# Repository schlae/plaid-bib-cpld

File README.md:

# The Plaid Bib CPLD edition - an Ad Lib MCA Clone

The Plaid Bib is a 100% compatible clone of the Ad Lib MCA sound card. This is
an Ad Lib card designed for Micro Channel Architecture machines, such as the
IBM PS/2 family and other compatibles from NCR, Tandy, Dell, and others.

Here are the design files. The BOM includes Mouser Electronics part numbers for
everything except for the YM3812 and the Y3014B, both of which are available
from brokers in China such as UTSource.

[Schematic](https://github.com/schlae/plaid-bib-cpld/blob/master/PlaidBibCPLD.pdf)

[Bill of Materials](https://github.com/schlae/plaid-bib-cpld/blob/master/PlaidBibCPLD.csv)

[Fab Files](https://github.com/schlae/plaid-bib-cpld/blob/master/fab/PlaidBibCPLD-fab.zip)

The logic family used for U1 is critical. Do not substitute LS, HC, HCT, or
similarly slow logic families. Use ALS, ACT, AHCT, or even F.

It's a good idea to use sockets for all the DIP chips just in case you need
to swap parts out.

## CPLD Notes
The Plaid Bib uses a CPLD (Complex Programmable Logic Device) to interface
between the MCA bus and the YM3812 synthesizer chip. Compared with the original
design that uses the 82C611 interface chip, this version is much simpler and
incorporates much of the external logic into a single device.

The CPLD must be programmed with the bitstream before you can use the card.
[You can find the bitstream here.](https://github.com/schlae/plaid-bib-cpld/blob/master/cpld/mcadlib.jed)

I've had good luck using the Linux command line program 'xc3sprog' with a
FTDI FT2232H Mini Module [datasheet here](https://www.ftdichip.com/Support/Documents/DataSheets/Modules/DS_FT2232H_Mini_Module.pdf).

Wiring for the FT2232H mini module:

| Point 1    | Point 2          | Description           |
| ---------- | ---------------- | --------------------- |
| CN2 pin 1  | CN2 pin 11       | V3V3 to VIO strap     |
| CN3 pin 1  | CN3 pin 3        | VBUS to VCC strap     |
| CN2 pin 3  | CN3 pin 12       | V3V3 to VIO strap (2) |
| CN2 pin 5  | JTAG cable pin 6 | V3V3 to Plaid Bib (optional) |
| CN2 pin 2  | JTAG cable pin 5 | GND                   |
| CN2 pin 7  | JTAG cable pin 4 | AD0, aka TCK          |
| CN2 pin 9  | JTAG cable pin 3 | AD2, aka TDO          |
| CN2 pin 10 | JTAG cable pin 2 | AD1, aka TDI          |
| CN2 pin 12 | JTAG cable pin 1 | AD3, aka TMS          |

You need to provide external power to the Plaid Bib through the 3.3V wire on the
programming header. The optional wire does this, or you can use a bench supply.

I obtained xc3sprog [here](https://github.com/matrix-io/xc3sprog). You can
compile and run this program on a Raspberry Pi using the Pi GPIO lines instead
of the FTDI mini module. In my case, I chose to patch it (TBD) to remove
references to the Pi GPIO library and ran it on a regular Linux PC.

Using the FTDI mini module, programming is quite simple. Connect the cable to
the assembled Plaid Bib board, then run the following command.

`xc3sprog -c ftdi -v mcadlib.jed`

If you run into issues with the cable not being detected, check your udev rules.
In theory you could run xc3sprog as root, but that's bad practice. ;)

### Building the CPLD Project
If you're feeling particularly masochistic, you can try building the CPLD
project using the Xilinx ISE Webpack tools. Because the ISE Webpack only
supports Ubuntu 14.7, it's simplest to run the program from a Docker container.
I use [docker-xilinx](https://github.com/jimmo/docker-xilinx).

### How the CPLD Works
This isn't meant to be an exhaustive tutorial on how Micro Channel bus works,
but here are a few basic functions the CPLD provides:
- Card setup and POS (programmable option select)
- Address decoding logic
- MCA bus logic interface to the YM3812
- A clock divider to provide 3.57MHz to the YM3812

Each card implements several 8-bit registers (POS registers). Two of these
registers are fixed and implement the 16-bit card ID value, which is how the
BIOS and the reference disk software identify the card. The remaining POS
registers can be used for any configuration-related function and are designed
to replace configuration jumpers. The meanings of each register bit are up
to the card designer, with the exception of a reserved bit that is used by
the BIOS to enable or disable a card; this way, the BIOS can resolve conflicts
automatically. Typically POS register bits control IO and memory address
assignments, IRQ lines, and so forth.

The CPLD implements the two required ID registers as well as two additional
POS registers. The first contains only a single bit -- the card enable signal.
The second register programs bits [8:4] of the I/O address. This should always
be 0xC0 so that the card appears at 0x388/0x389.

When you add a new card to a MCA bus system, the BIOS detects the new card
and requires you to run the reference disk configuration program. This program
searches for an ADF file associated with the new card. The ADF file is
human-readable text that tells the BIOS which I/O address, IRQ, etc match up
with each POS register bit. The reference disk program uses this information to
find a configuration for all the cards in the computer so that none of them
conflict with each other. When it's done, it writes the raw POS register values
along with the card ID values to the battery-backed SRAM on the motherboard.

The CPLD decodes the I/O address (0x388 and 0x389) to ensure the card only
responds when it is addressed directly by the computer. On the MCA bus, the
address lines and control lines (s0 and s1 aka write and read) get latched
on the falling edge of the ADL# (address latch) control line.

The data transfer itself begins a little later with the falling edge of the
CMD# control line and ends with rising edge. MCA pipelines address and data;
during the data transfer, the MCA prepares the address for the next bus
transfer! The CPLD turns these signals into the typical asynchronous transfer
used by the YM3812.

Finally, the CPLD takes the MCA bus 14.3MHz clock signal and divides it by 4
to get the 3.57MHz clock used by the YM3812.

## Bracket
MCA brackets are no longer available. You have a few options:
- Remove the bracket from an existing card, like a token ring card or something
- 3D print the bracket
- Use the card without a bracket at all

If you want to print your own, here are STEP models of the bracket and the
plastic clip.

[Bracket](https://github.com/schlae/plaid-bib/blob/master/mech/MCABracket.STEP)

[Clip](https://github.com/schlae/plaid-bib/blob/master/mech/MCAClip.STEP)

Please note that neither file is designed specifically for 3D printing; they're
meant to match the real hardware exactly. The clip might print just fine, but
the bracket is probably too thin to print well.

## Compatibility
The Plaid Bib has been tested on some models of PS/2. More to be added as
people provide test reports.

| Computer           | Model    | CPU          | Adapters | Compatible ? |
| ------------------ | -------- | ------------ | -------- | ------------ |
| IBM PS/2 Model 50  | 8550-021 | 80286-10     | | Partial¹
| IBM PS/2 Model 50Z | 8550-031 | 80286-10     | Hard disk (ID:DF9F), IBM SCSI 71G3575 | Yes |
| IBM PS/2 Model 55SX with Reply Turboboard| 8555 | 486SLC2-50 |  | Yes |
| IBM PS/2 Model 70  | 8570-E61 | 386-16   | Adaptec AHA-1640 | Yes |
| IBM PS/2 Model 70  | 8570-121 | 386-20   | | Yes |
| IBM PS/2 Model 80  | 8580-071 | 386DX-16   | | Yes² |
| IBM PS/2 Model 85  | 9585     | 486SX-33     | | Yes |
| IBM PS/2 Model 95  | 8595     | 486DX2-50    | | Yes |

¹One user reported compatibility problems with the hard drive (ID:DF9F)

²PS/2 Model 80 machines with the type 1 planar (16MHz 386) and an installed
MCA memory card may have compatibility issues; the Plaid Bib behaves
erratically in one user's machine, but works fine in another one.

## Installation
You will need the ADF (adapter description file) in order to set up the Plaid
Bib on your MCA computer.

[Plaid Bib ADF](https://github.com/schlae/plaid-bib/blob/master/@70D7.ADF)

Place the file on a 3 1/2" floppy disk. After you install the card and boot
the computer, it will detect that a new card has been installed and prompt
you to insert the reference disk. Do this and follow the prompts. When the
setup utility asks you to insert the option disk, use the one that contains
the ADF file. After the setup utility configures the card, it will prompt
you to reboot the machine.

Once that's finished, try out the Plaid Bib with your favorite game!

## Troubleshooting
Keep in mind that Micro Channel systems can be difficult to troubleshoot due to
the large number of possible configurations and the varied implementations of
the bus. Not all games will even work on some PS/2 systems, even without a
sound card!

Here are a few things to try out first before you really start digging in:
- Is the CPLD soldered in correctly, with no solder bridges? If you have a
microscope, check every solder joint! Did you program the CPLD?
- Are there any bad or fake chips? Some users have reported issues with fake
74ALS245 buffer chips, fake YM3812s, and fake Y3014B chips
- Try running [SBDIAG](https://github.com/schlae/snark-barker/tree/master/sbdiag)

### Symptom-by-Symptom

**Computer will not boot at all, Computer boots but does not detect the card**

Suspect the CPLD. Check for bad solder joints. Is pin 1 oriented correctly?
Compare it with the photo.

Did you use something other than a 74ALS245, 'ACT245, 'AHCT245, or 'F245?
Slower logic families can "crash the bus" and prevent the system from booting.

**The card causes random errors with the hard disk, or with other cards**

Did you buy a legitimate 74ALS245, or is it a fake? Try swapping it out.

## License
This work is licensed under a Creative Commons Attribution-ShareAlike 4.0
International License. See [https://creativecommons.org/licenses/by-sa/4.0/](https://creativecommons.org/licenses/by-sa/4.0/).

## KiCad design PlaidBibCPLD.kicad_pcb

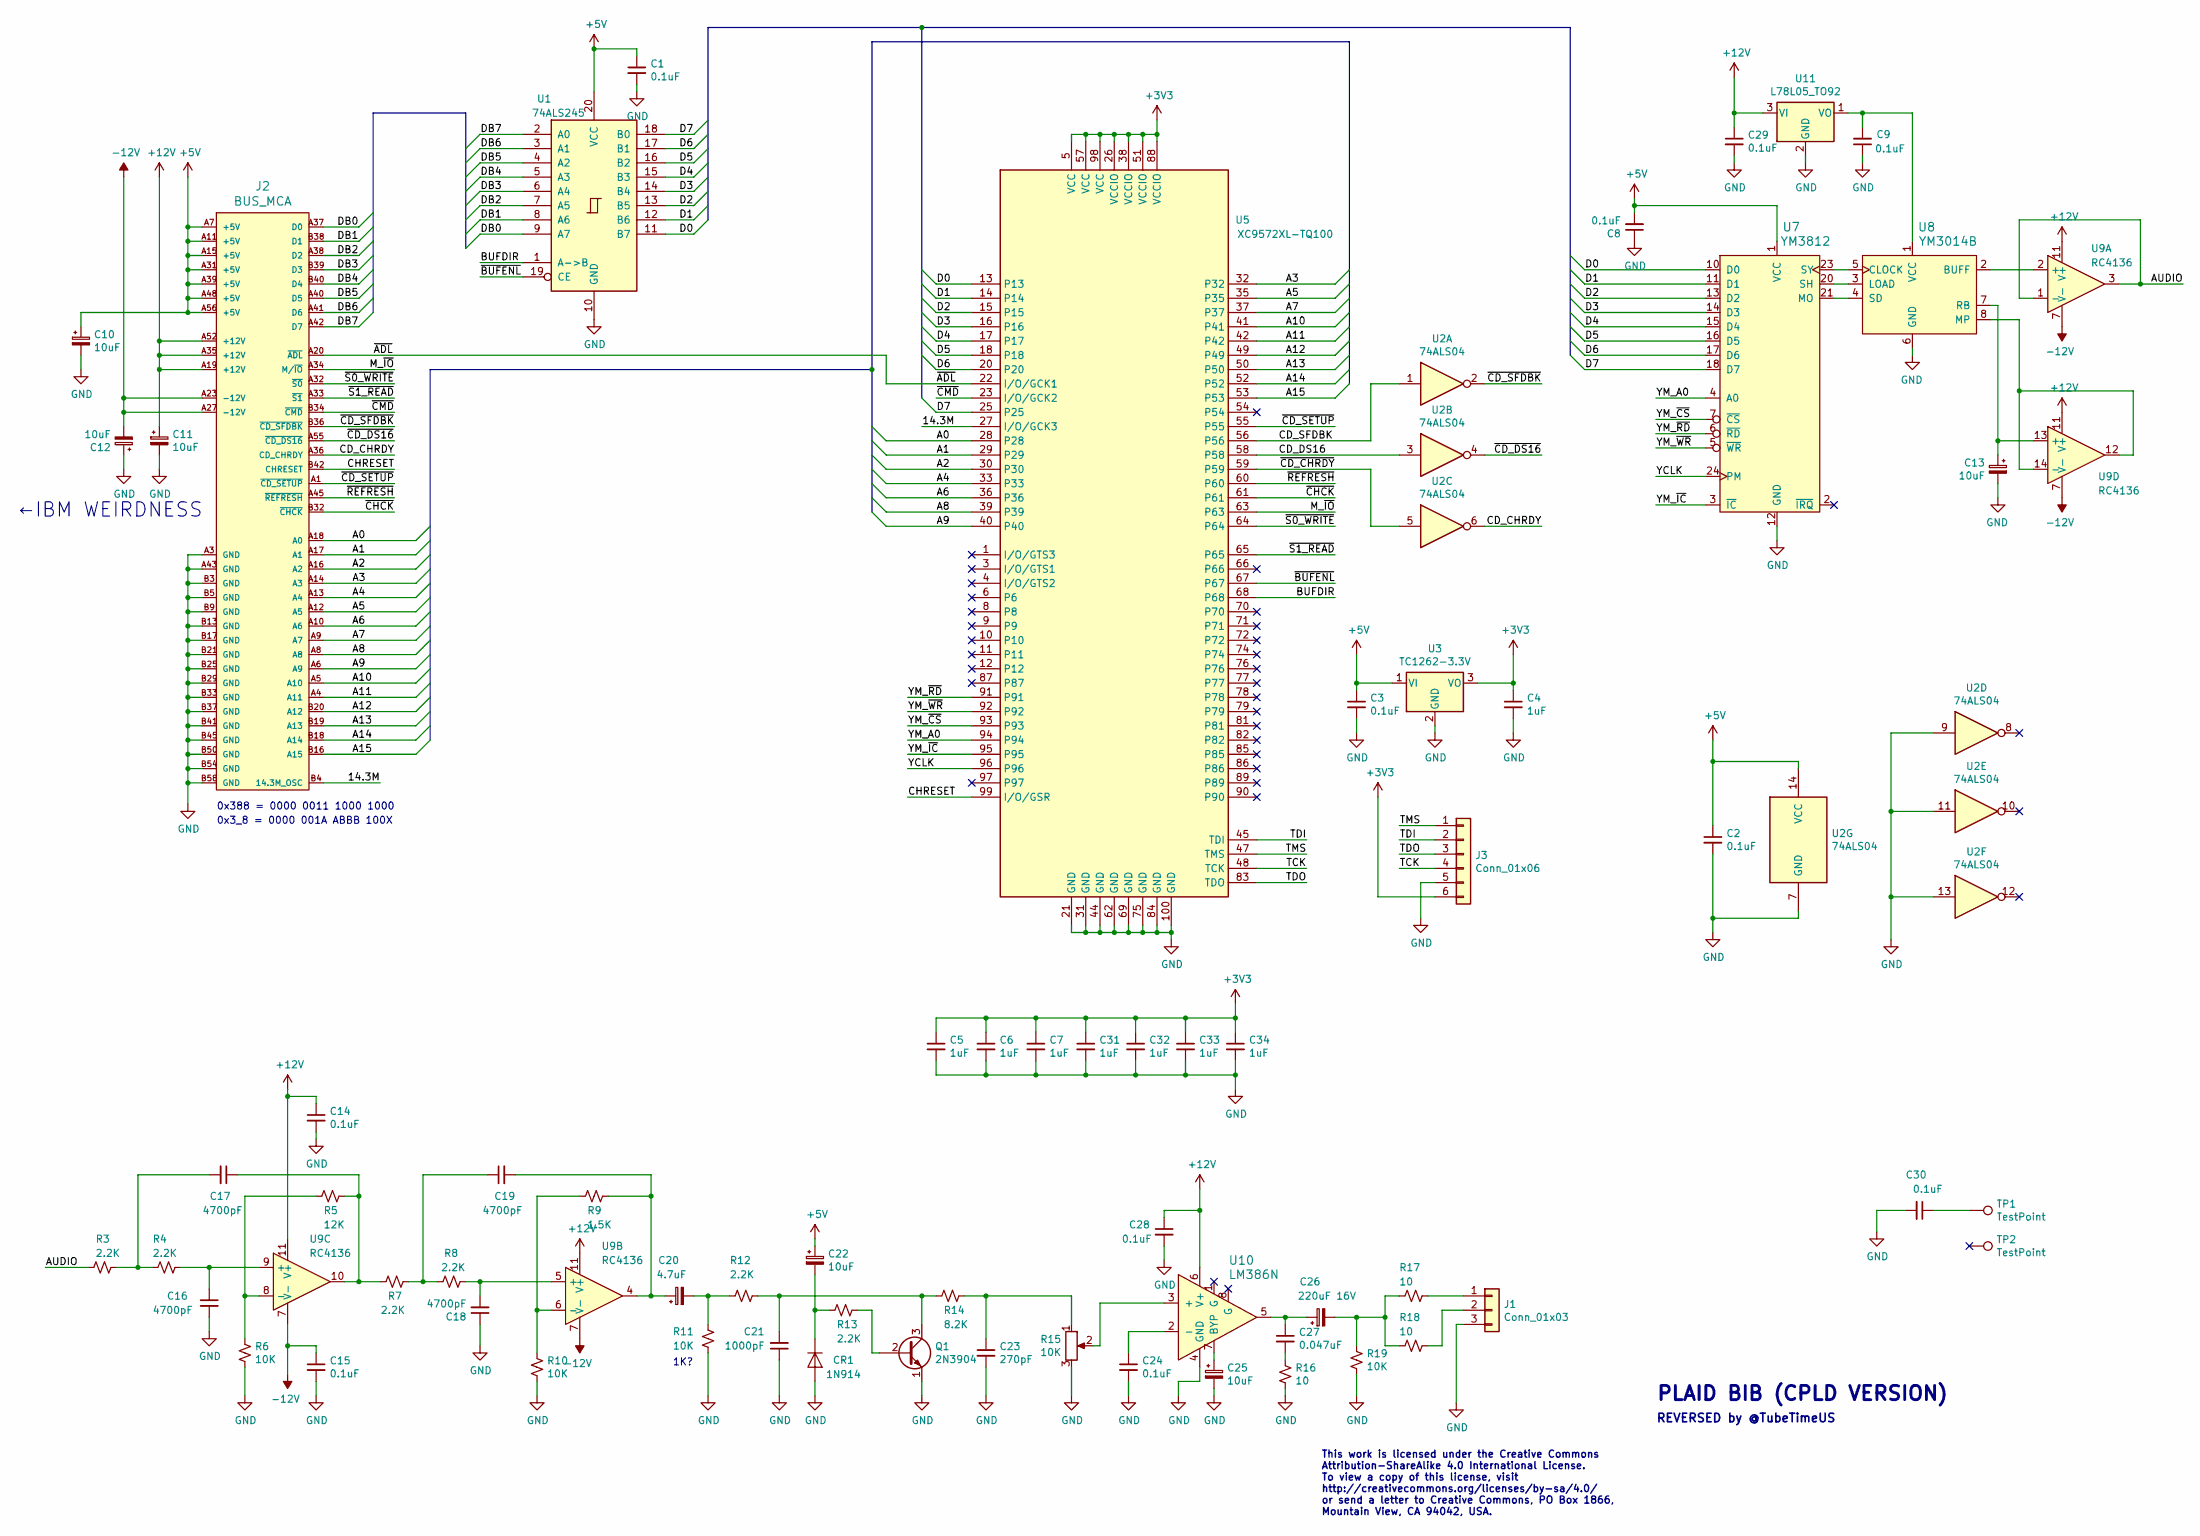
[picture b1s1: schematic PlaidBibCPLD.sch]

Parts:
C1, C2, C3, C8, C9, C14, C15, C24, C28, C29, C30: 0.1uF; CAP23; Mouser 581-AR215C104K4R
C4, C5, C6, C7, C31, C32, C33, C34: 1uF; CAP23; Mouser 581-AR215C104K4R
C10, C11, C12, C13, C22, C25: 10uF; CAPAP200; Mouser 581-TAP106M025CRW
C16, C17, C18, C19: 4700pF; CAP23; Mouser 581-AR211C472K4R
C20: 4.7uF; CAPAP200; Mouser 581-TAP475K016SCS
C21: 1000pF; CAP23; Mouser 581-AR211C102K4R
C23: 270pF; CAP23; Mouser 594-S271K43SL0N6TK5R
C26: 220uF 16V; CAPA1000; Mouser 647-TVX1C221MAD
C27: 0.047uF; CAP23; Mouser 581-AR215C473K4R
CR1: 1N914; DIOA500; Mouser 512-1N914
J1: Conn_01x03; SJ1-3553; Mouser 490-SJ1-3553NG
J2: BUS_MCA; BUS_MCA_ADLIB
J3: Conn_01x06; Pin_Header_Straight_1x06_Pitch2.54mm
Q1: 2N3904; TO92-IL; Mouser 512-2N3904BU
R3, R4, R7, R8, R12, R13: 2.2K; RESA500; Mouser 291-2.2K-RC
R5: 12K; RESA500; Mouser 291-12K-RC
R6, R10, R11, R19: 10K; RESA500; Mouser 291-10K-RC
R9: 1.5K; RESA500; Mouser 291-1.5K-RC
R14: 8.2K; RESA500; Mouser 291-8.2K-RC
R15: 10K; RK14J11A000G; Mouser 688-RK14J11A000G
R16, R17, R18: 10; RESA500; Mouser 291-10-RC
TP1, TP2: TestPoint; MH_125
U1: 74ALS245; DIP300_20N; Mouser 595-SN74ALS245AN
U2: 74ALS04; DIP254P762X635-14; Mouser 595-SN74ALS04BN
U3: TC1262-3.3V; SOT230P700X170-3; Mouser 579-TC1262-3.3VDB
U5: XC9572XL-TQ100; TQFP50P1600X1600X140-100; Mouser 217-9572XL-10TQG100C
U7: YM3812; DIP600_24N
U8: YM3014B; DIP300_8N
U9: RC4136; DIP300_14N; Mouser 595-RC4136N
U10: LM386N; DIP300_8N; Mouser 926-LM386N-4/NOPB
U11: L78L05_TO92; TO92-IL; Mouser 511-L78L05ACZ

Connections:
+3V3: C4.1, C5.1, C6.1, C7.1, C31.1, C32.1, C33.1, C34.1, J3.6, U3.3 (VO), U5.5 (VCC), U5.26 (VCCIO), U5.38 (VCCIO), U5.51 (VCCIO), U5.57 (VCC), U5.88 (VCCIO), U5.98 (VCC)
+5V: C1.1, C2.1, C3.1, C8.2, C10.1, C22.1, J2.A7 (+5V), J2.A11 (+5V), J2.A15 (+5V), J2.A31 (+5V), J2.A39 (+5V), J2.A48 (+5V), J2.A56 (+5V), U1.20 (VCC), U2.14 (VCC), U3.1 (VI), U7.1 (VCC)
+12V: C11.1, C14.1, C28.1, C29.1, J2.A19 (+12V), J2.A35 (+12V), J2.A52 (+12V), U9.11 (V+), U10.6 (V+), U11.3 (VI)
-12V: C12.2, C15.1, J2.A23 (-12V), J2.A27 (-12V), U9.7 (V-)
/14.3M: J2.B4 (14.3M_OSC), U5.27 (I/O/GCK3)
/A0: J2.A18 (A0), U5.28
/A1: J2.A17 (A1), U5.29
/A2: J2.A16 (A2), U5.30
/A3: J2.A14 (A3), U5.32
/A4: J2.A13 (A4), U5.33
/A5: J2.A12 (A5), U5.35
/A6: J2.A10 (A6), U5.36
/A7: J2.A9 (A7), U5.37
/A8: J2.A8, U5.39
/A9: J2.A6 (A9), U5.40
/A10: J2.A5 (A10), U5.41
/A11: J2.A4 (A11), U5.42
/A12: J2.B20 (A12), U5.49
/A13: J2.B19 (A13), U5.50
/A14: J2.B18 (A14), U5.52
/A15: J2.B16 (A15), U5.53
/AUDIO: R3.2, U9.1 (-), U9.3
/BUFDIR: U1.1 (A->B), U5.68
/CD_CHRDY: J2.A36 (CD_CHRDY), U2.6
/CD_DS16: U2.3, U5.58
/CD_SFDBK: U2.1, U5.56
/CHRESET: J2.B42 (CHRESET), U5.99 (I/O/GSR)
/D0: U1.11 (B7), U5.13, U7.10 (D0)
/D1: U1.12 (B6), U5.14, U7.11 (D1)
/D2: U1.13 (B5), U5.15, U7.13 (D2)
/D3: U1.14 (B4), U5.16, U7.14 (D3)
/D4: U1.15 (B3), U5.17, U7.15 (D4)
/D5: U1.16 (B2), U5.18, U7.16 (D5)
/D6: U1.17 (B1), U5.20, U7.17 (D6)
/D7: U1.18 (B0), U5.25, U7.18 (D7)
/DB0: J2.A37 (D0), U1.9 (A7)
/DB1: J2.B38 (D1), U1.8 (A6)
/DB2: J2.A38 (D2), U1.7 (A5)
/DB3: J2.B39 (D3), U1.6 (A4)
/DB4: J2.B40 (D4), U1.5 (A3)
/DB5: J2.A40 (D5), U1.4 (A2)
/DB6: J2.A41 (D6), U1.3 (A1)
/DB7: J2.A42 (D7), U1.2 (A0)
/M_~IO: J2.A34 (M/~IO), U5.63
/TCK: J3.4, U5.48 (TCK)
/TDI: J3.2, U5.45 (TDI)
/TDO: J3.3, U5.83 (TDO)
/TMS: J3.1, U5.47 (TMS)
/YCLK: U5.96, U7.24 (PM)
/YM_A0: U5.94, U7.4 (A0)
/YM_~CS: U5.93, U7.7 (~CS)
/YM_~IC: U5.95, U7.3 (~IC)
/YM_~RD: U5.91, U7.6 (~RD)
/YM_~WR: U5.92, U7.5 (~WR)
/~ADL: J2.A20 (~ADL), U5.22 (I/O/GCK1)
/~BUFENL: U1.19 (CE), U5.67
/~CD_CHRDY: U2.5, U5.59
/~CD_DS16: J2.A55 (~CD_DS16), U2.4
/~CD_SETUP: J2.A1 (~CD_SETUP), U5.55
/~CD_SFDBK: J2.B36 (~CD_SFDBK), U2.2
/~CHCK: J2.B32 (~CHCK), U5.61
/~CMD: J2.B34 (~CMD), U5.23 (I/O/GCK2)
/~REFRESH: J2.A45 (~REFRESH), U5.60
/~S0_WRITE: J2.A32 (~S0), U5.64
/~S1_READ: J2.A33 (~S1), U5.65
GND: C1.2, C2.2, C3.2, C4.2, C5.2, C6.2, C7.2, C8.1, C9.1, C10.2, C11.2, C12.1, C13.2, C14.2, C15.2, C16.2, C18.1, C21.1, C23.2, C24.2, C25.2, C28.2, C29.2, C30.2, C31.2, C32.2, C33.2, C34.2, CR1.2 (A), J1.3, J2.A3 (GND), J2.A43 (GND), J2.B3 (GND), J2.B5 (GND), J2.B9 (GND), J2.B13 (GND), J2.B17 (GND), J2.B21 (GND), J2.B25 (GND), J2.B29 (GND), J2.B33 (GND), J2.B37 (GND), J2.B41 (GND), J2.B45 (GND), J2.B50 (GND), J2.B54 (GND), J2.B58 (GND), J3.5, Q1.1 (E), R6.2, R10.2, R11.2, R15.3, R16.2, R19.2, U1.10 (GND), U2.7 (GND), U2.9, U2.11, U2.13, U3.2 (GND), U5.21 (GND), U5.31 (GND), U5.44 (GND), U5.62 (GND), U5.69 (GND), U5.75 (GND), U5.84 (GND), U5.100 (GND), U7.12 (GND), U8.6 (GND), U10.4 (GND), U11.2 (GND)
unnamed: C9.2, U8.1 (VCC), U11.1 (VO)
unnamed: C13.1, U8.7 (RB), U9.13 (+)
unnamed: C16.1, R4.1, U9.9 (+)
unnamed: C17.1, R5.1, R7.2, U9.10
unnamed: C17.2, R3.1, R4.2
unnamed: C18.2, R8.2, U9.5 (+)
unnamed: C19.1, R7.1, R8.1
unnamed: C19.2, C20.1, R9.1, U9.4
unnamed: C20.2, R11.1, R12.2
unnamed: C21.2, Q1.3 (C), R12.1, R14.2
unnamed: C22.2, CR1.1 (K), R13.2
unnamed: C23.1, R14.1, R15.1
unnamed: C24.1, U10.2 (-)
unnamed: C25.1, U10.7 (BYP)
unnamed: C26.1, C27.1, U10.5
unnamed: C26.2, R17.1, R18.1, R19.1
unnamed: C27.2, R16.1
unnamed: C30.1, TP1.1
unnamed: J1.1, R17.2
unnamed: J1.2, R18.2
unnamed: Q1.2 (B), R13.1
unnamed: R5.2, R6.1, U9.8 (-)
unnamed: R9.2, R10.1, U9.6 (-)
unnamed: R15.2, U10.3 (+)
unnamed: U7.20 (SH), U8.3 (LOAD)
unnamed: U7.21 (MO), U8.4 (SD)
unnamed: U7.23 (SY), U8.5 (CLOCK)
unnamed: U8.2 (BUFF), U9.2 (+)
unnamed: U8.8 (MP), U9.12, U9.14 (-)

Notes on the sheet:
0x388 = 0000 0011 1000 1000
1K?
←IBM WEIRDNESS
0x3_8 = 0000 001A ABBB 100X
PLAID BIB (CPLD VERSION)
REVERSED by @TubeTimeUS
This work is licensed under the Creative Commons Attribution-ShareAlike 4.0 International License. To view a copy of this license, visit http://creativecommons.org/licenses/by-sa/4.0/ or send a letter to Creative Commons, PO Box 1866, Mountain View, CA 94042, USA.

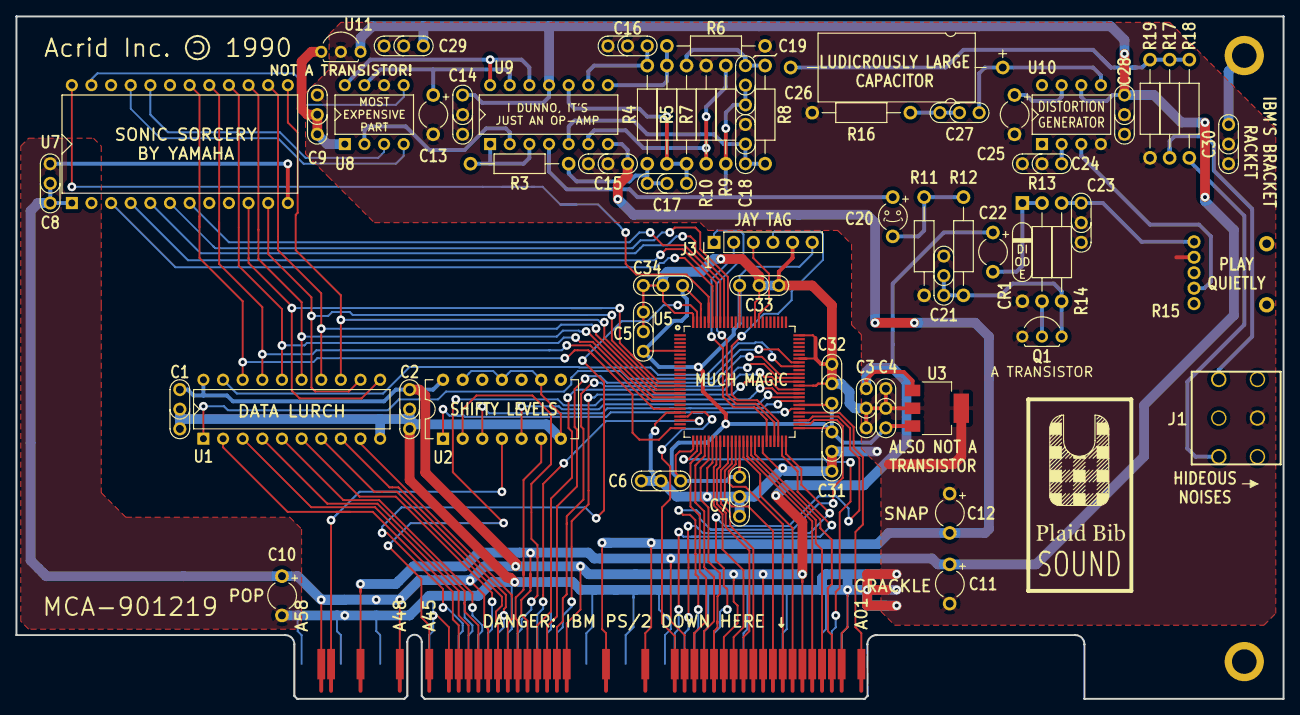
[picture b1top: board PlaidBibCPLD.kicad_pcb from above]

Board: 2 copper layers, 163.9 x 88.3 mm, 67 parts (0 on the bottom side), 95 nets.

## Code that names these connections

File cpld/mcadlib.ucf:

#
# Plaid Bib CPLD Version - Constraints (pin mapping)
# Copyright (c) 2020 Eric Schlaepfer
# This work is licensed under the Creative Commons Attribution-ShareAlike 4.0
# International License. To view a copy of this license, visit
# http://creativecommons.org/licenses/by-sa/4.0/ or send a letter to Creative
# Commons, PO Box 1866, Mountain View, CA 94042, USA.
#

# Pin map
NET "adl_l" loc="P22";
NET "adl_l" BUFG=CLK;
NET "cmd" loc="P23";
NET "cmd" BUFG=CLK;
NET "ext_clock" loc="P27";
NET "ext_clock" BUFG=CLK;

NET "cd_setup_l" loc="P55";
NET "cd_sfdbk" loc="P56";
NET "cd_ds16" loc="P58";
NET "cd_chrdy_l" loc="P59";

NET "m_io" loc="P63";
NET "s0_w_l" loc="P64";
NET "s1_r_l" loc="P65";
NET "a(0)" loc="P28";
NET "a(1)" loc="P29";
NET "a(2)" loc="P30";
NET "a(3)" loc="P32";
NET "a(4)" loc="P33";
NET "a(5)" loc="P35";
NET "a(6)" loc="P36";
NET "a(7)" loc="P37";
NET "a(8)" loc="P39";
NET "a(9)" loc="P40";
NET "a(10)" loc="P41";
NET "a(11)" loc="P42";
NET "a(12)" loc="P49";
NET "a(13)" loc="P50";
NET "a(14)" loc="P52";
NET "a(15)" loc="P53";

NET "d(0)" loc="P13";
NET "d(1)" loc="P14";
NET "d(2)" loc="P15";
NET "d(3)" loc="P16";
NET "d(4)" loc="P17";
NET "d(5)" loc="P18";
NET "d(6)" loc="P20";
NET "d(7)" loc="P25";

NET "ior_l" loc="P91";
NET "iow_l" loc="P92";
NET "ym_cs_l" loc="P93";
NET "ym_a0" loc="P94";
NET "ym_ic_l" loc="P95";
NET "ym_clock" loc="P96";

NET "cden" loc="P66";
NET "bufen_l" loc="P67";
NET "bufdir" loc="P68";

NET "chreset" loc="P99";

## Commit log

2020-01-08 initial empty commit
2020-01-09 add readme
2020-01-27 Update readme to include Model 85 test result
2020-02-13 Update readme to include Model 95
2020-02-15 Update readme to include Model 80 test result
2020-02-16 Update readme regarding Model 80 issues
2020-02-23 Correct Mouser part number for 1uF capacitors
2020-03-08 Update readme regarding Model 80 and Model 55SX
2020-12-17 Add ISE project file
2020-12-18 Update compatibility list
2020-12-18 Formatting fix
2020-12-18 Formatting
2021-03-30 Use hard-coded base address
2021-07-22 Update compatibility list, add troubleshooting info

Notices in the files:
PlaidBibCPLD.kicad_pcb:
Copyright (C) 2019 Eric Schlaepfer
CC BY-SA (Attribution-ShareAlike)
